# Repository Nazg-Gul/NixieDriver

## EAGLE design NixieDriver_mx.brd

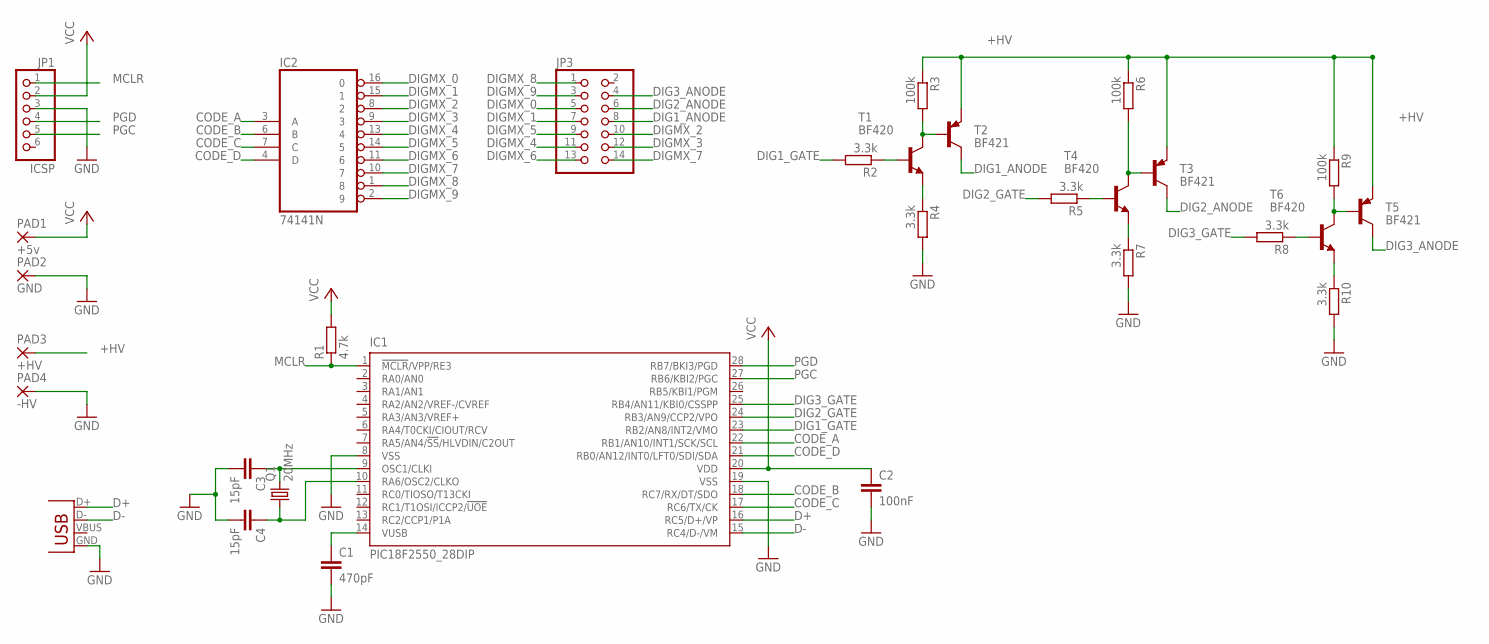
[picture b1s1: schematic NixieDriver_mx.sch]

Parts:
C1: 470pF; C050-024X044
C2: 100nF; C050-024X044
C3, C4: 15pF; C050-024X044
IC1: PIC18F2550_28DIP; DIL28-3
IC2: 74141N; DIL16
JP1: ICSP; 1X06
JP3: PINHD-2X7; 2X07
PAD1: +5v; SMD2,54-5,08
PAD2: GND; SMD2,54-5,08
PAD3: +HV; SMD2,54-5,08
PAD4: -HV; SMD2,54-5,08
Q1: 20MHz; HC49/S
R1: 4.7k; 0207/2V
R2, R5, R8: 3.3k; 0207/2V
R3, R6, R9: 100k; 0207/5V
R4, R7, R10: 3.3k; 0207/7
T1, T4, T6: BF420; TO92-ECB
T2, T3, T5: BF421; TO92-ECB
X1: USB-B-H

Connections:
+HV: PAD3.1, R3.1, R6.1, R9.1, T2.E, T3.E, T5.E
CODE_A: IC1.22 (RB1/AN10/INT1/SCK/SCL), IC2.3 (A)
CODE_B: IC1.18 (RC7/RX/DT/SDO), IC2.6 (B)
CODE_C: IC1.17 (RC6/TX/CK), IC2.7 (C)
CODE_D: IC1.21 (RB0/AN12/INT0/LFT0/SDI/SDA), IC2.4 (D)
D+: IC1.16 (RC5/D+/VP), X1.D+
D-: IC1.15 (RC4/D-/VM), X1.D-
DIG1_ANODE: JP3.8, T2.C
DIG1_GATE: IC1.23 (RB2/AN8/INT2/VMO), R2.2
DIG2_ANODE: JP3.6, T3.C
DIG2_GATE: IC1.24 (RB3/AN9/CCP2/VPO), R5.2
DIG3_ANODE: JP3.4, T5.C
DIG3_GATE: IC1.25 (RB4/AN11/KBI0/CSSPP), R8.2
DIGMX_0: IC2.16 (0), JP3.5
DIGMX_1: IC2.15 (1), JP3.7
DIGMX_2: IC2.8 (2), JP3.10
DIGMX_3: IC2.9 (3), JP3.12
DIGMX_4: IC2.13 (4), JP3.11
DIGMX_5: IC2.14 (5), JP3.9
DIGMX_6: IC2.11 (6), JP3.13
DIGMX_7: IC2.10 (7), JP3.14
DIGMX_8: IC2.1 (8), JP3.1
DIGMX_9: IC2.2 (9), JP3.3
GND: C1.2, C2.2, C3.2, C4.2, IC1.8 (VSS), IC1.19 (VSS), IC2.12 (GND), JP1.3, PAD2.1, PAD4.1, R4.2, R7.2, R10.2, X1.GND
MCLR: IC1.1 (!MCLR!/VPP/RE3), JP1.1, R1.1
unnamed: C1.1, IC1.14 (VUSB)
unnamed: C3.1, IC1.9 (OSC1/CLKI), Q1.2
unnamed: C4.1, IC1.10 (RA6/OSC2/CLKO), Q1.1
unnamed: R3.2, T1.C, T2.B
unnamed: R2.1, T1.B
unnamed: R4.1, T1.E
unnamed: R6.2, T3.B, T4.C
unnamed: R7.1, T4.E
unnamed: R5.1, T4.B
unnamed: R9.2, T5.B, T6.C
unnamed: R10.1, T6.E
unnamed: R8.1, T6.B
PGC: IC1.27 (RB6/KBI2/PGC), JP1.5
PGD: IC1.28 (RB7/BKI3/PGD), JP1.4
VCC: C2.1, IC1.20 (VDD), IC2.5 (VCC), JP1.2, PAD1.1, R1.2

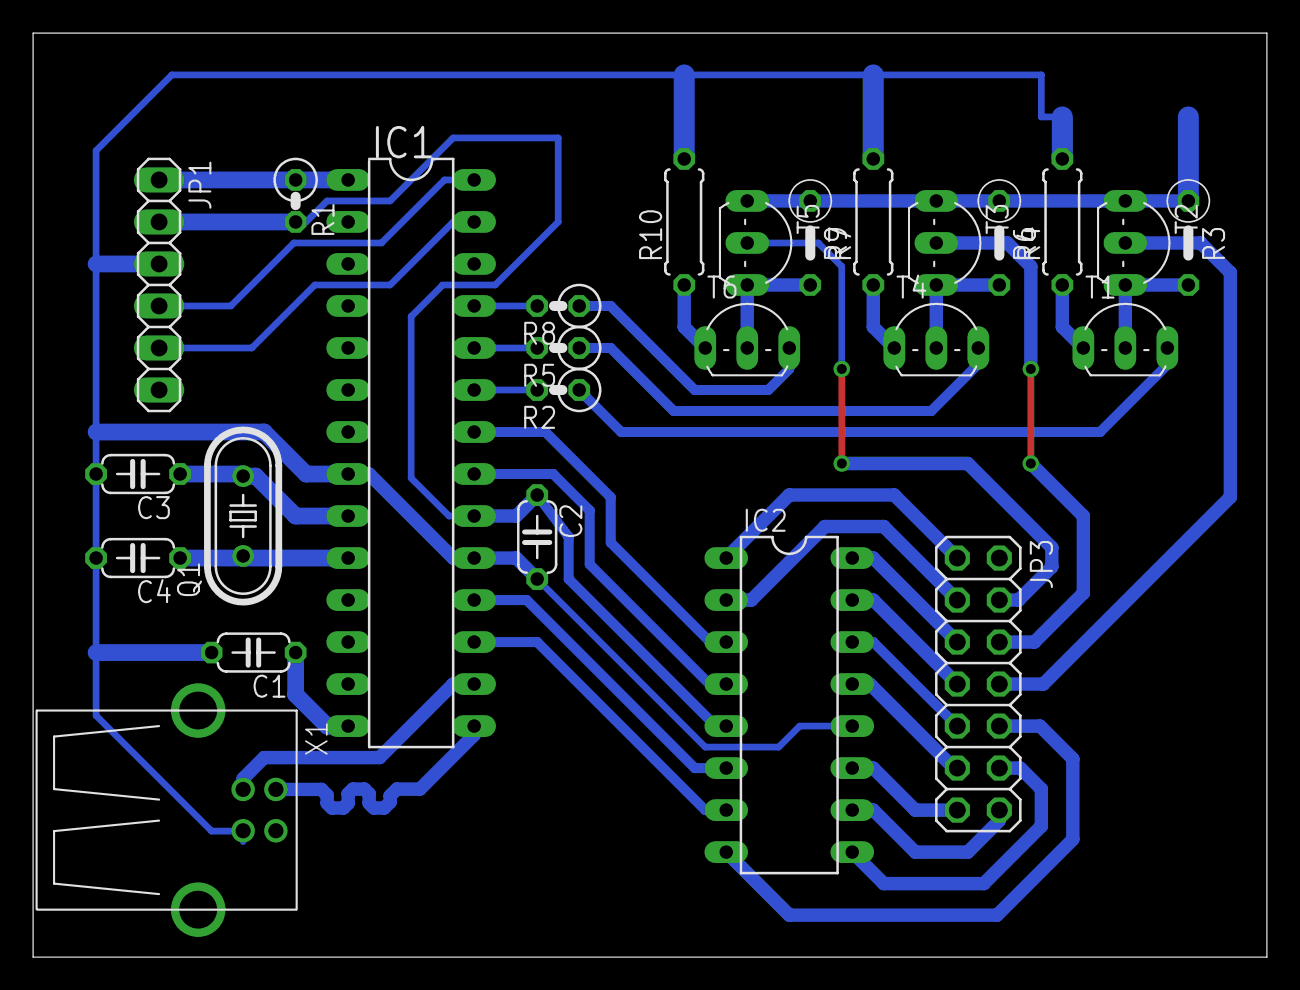
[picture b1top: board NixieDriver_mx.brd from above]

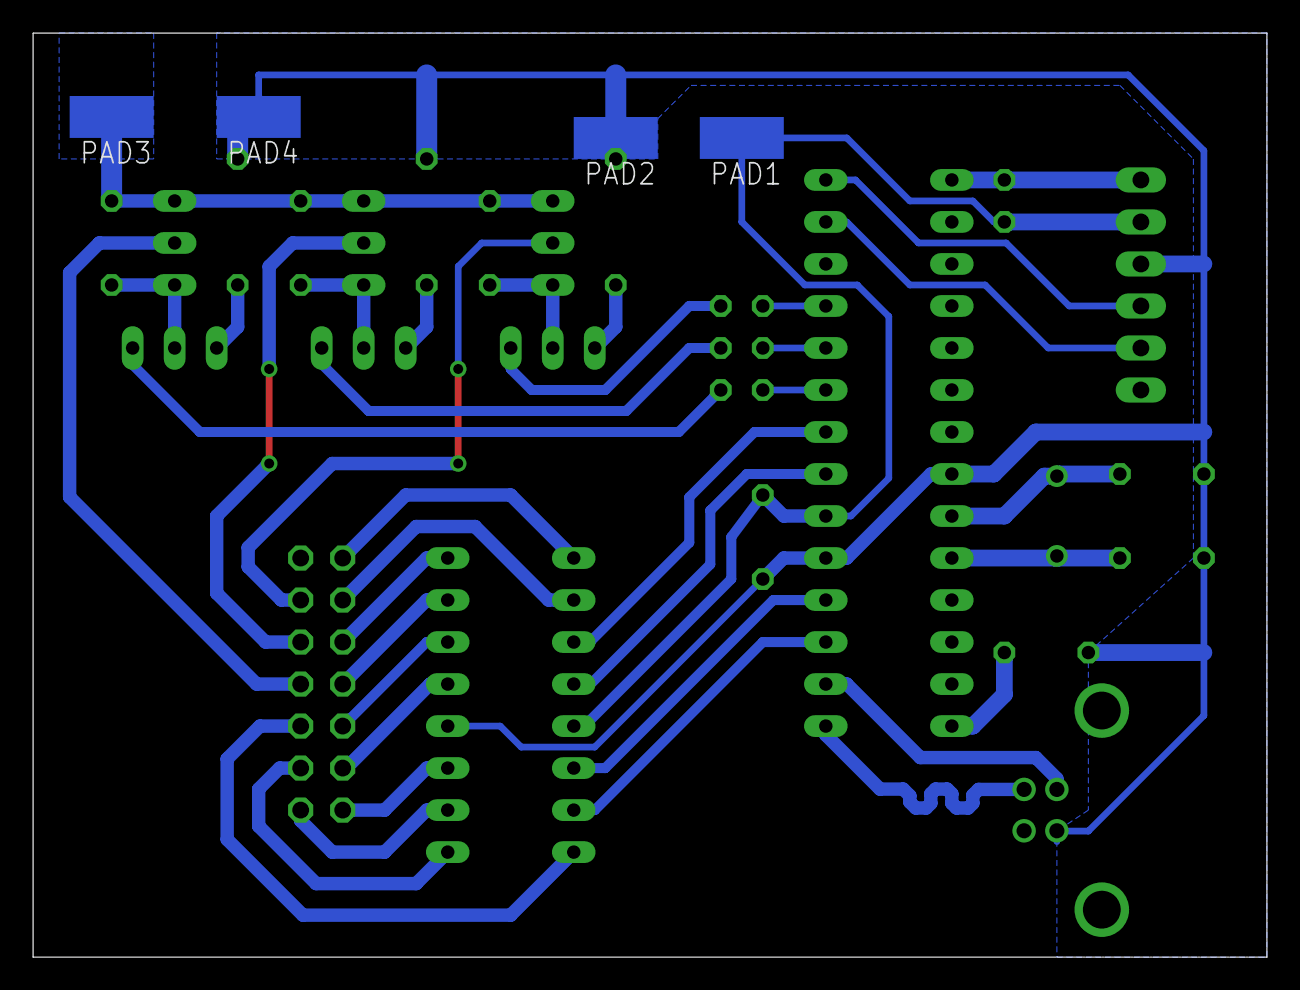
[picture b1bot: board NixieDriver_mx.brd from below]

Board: 2 copper layers, 74.6 x 55.9 mm, 30 parts (4 on the bottom side), 40 nets.

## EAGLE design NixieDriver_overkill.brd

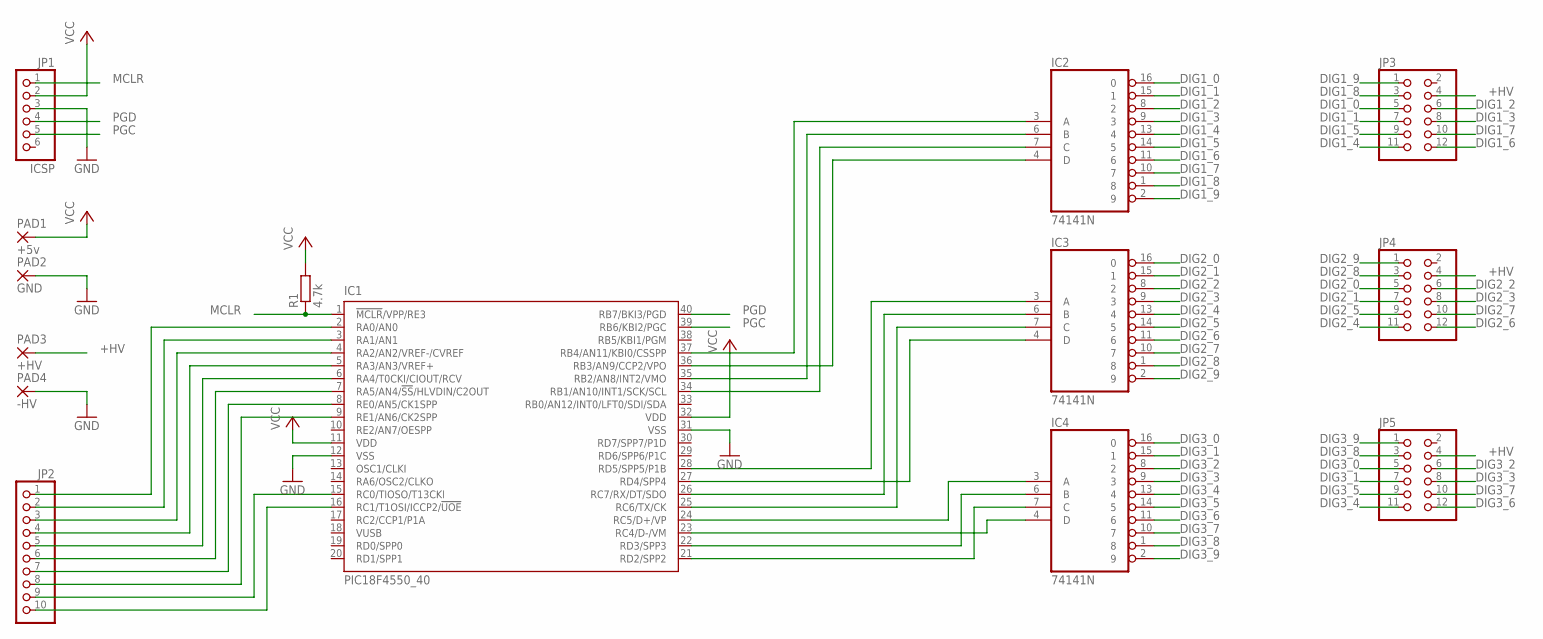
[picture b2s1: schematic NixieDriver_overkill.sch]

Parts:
IC1: PIC18F4550_40; DIL40
IC2, IC3, IC4: 74141N; DIL16
JP1: ICSP; 1X06
JP2: PINHD-1X10; 1X10
JP3, JP4, JP5: PINHD-2X6; 2X06
PAD1: +5v; SMD2,54-5,08
PAD2: GND; SMD2,54-5,08
PAD3: +HV; SMD2,54-5,08
PAD4: -HV; SMD2,54-5,08
R1: 4.7k; R1206

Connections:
+HV: JP3.4, JP4.4, JP5.4, PAD3.1
DIG1_0: IC2.16 (0), JP3.5
DIG1_1: IC2.15 (1), JP3.7
DIG1_2: IC2.8 (2), JP3.6
DIG1_3: IC2.9 (3), JP3.8
DIG1_4: IC2.13 (4), JP3.11
DIG1_5: IC2.14 (5), JP3.9
DIG1_6: IC2.11 (6), JP3.12
DIG1_7: IC2.10 (7), JP3.10
DIG1_8: IC2.1 (8), JP3.3
DIG1_9: IC2.2 (9), JP3.1
DIG2_0: IC3.16 (0), JP4.5
DIG2_1: IC3.15 (1), JP4.7
DIG2_2: IC3.8 (2), JP4.6
DIG2_3: IC3.9 (3), JP4.8
DIG2_4: IC3.13 (4), JP4.11
DIG2_5: IC3.14 (5), JP4.9
DIG2_6: IC3.11 (6), JP4.12
DIG2_7: IC3.10 (7), JP4.10
DIG2_8: IC3.1 (8), JP4.3
DIG2_9: IC3.2 (9), JP4.1
DIG3_0: IC4.16 (0), JP5.5
DIG3_1: IC4.15 (1), JP5.7
DIG3_2: IC4.8 (2), JP5.6
DIG3_3: IC4.9 (3), JP5.8
DIG3_4: IC4.13 (4), JP5.11
DIG3_5: IC4.14 (5), JP5.9
DIG3_6: IC4.11 (6), JP5.12
DIG3_7: IC4.10 (7), JP5.10
DIG3_8: IC4.1 (8), JP5.3
DIG3_9: IC4.2 (9), JP5.1
GND: IC1.12 (VSS), IC1.31 (VSS), IC2.12 (GND), IC3.12 (GND), IC4.12 (GND), JP1.3, PAD2.1, PAD4.1
MCLR: IC1.1 (!MCLR!/VPP/RE3), JP1.1, R1.1
unnamed: IC1.24 (RC5/D+/VP), IC4.3 (A)
unnamed: IC1.23 (RC4/D-/VM), IC4.4 (D)
unnamed: IC1.22 (RD3/SPP3), IC4.6 (B)
unnamed: IC1.21 (RD2/SPP2), IC4.7 (C)
unnamed: IC1.25 (RC6/TX/CK), IC3.7 (C)
unnamed: IC1.26 (RC7/RX/DT/SDO), IC3.6 (B)
unnamed: IC1.27 (RD4/SPP4), IC3.4 (D)
unnamed: IC1.28 (RD5/SPP5/P1B), IC3.3 (A)
unnamed: IC1.34 (RB1/AN10/INT1/SCK/SCL), IC2.7 (C)
unnamed: IC1.35 (RB2/AN8/INT2/VMO), IC2.6 (B)
unnamed: IC1.36 (RB3/AN9/CCP2/VPO), IC2.4 (D)
unnamed: IC1.37 (RB4/AN11/KBI0/CSSPP), IC2.3 (A)
unnamed: IC1.2 (RA0/AN0), JP2.1
unnamed: IC1.3 (RA1/AN1), JP2.2
unnamed: IC1.4 (RA2/AN2/VREF-/CVREF), JP2.3
unnamed: IC1.5 (RA3/AN3/VREF+), JP2.4
unnamed: IC1.6 (RA4/T0CKI/CIOUT/RCV), JP2.5
unnamed: IC1.7 (RA5/AN4/!SS!/HLVDIN/C2OUT), JP2.6
unnamed: IC1.8 (RE0/AN5/CK1SPP), JP2.7
unnamed: IC1.9 (RE1/AN6/CK2SPP), JP2.8
unnamed: IC1.15 (RC0/TIOSO/T13CKI), JP2.9
unnamed: IC1.16 (RC1/T1OSI/ICCP2/!UOE), JP2.10
PGC: IC1.39 (RB6/KBI2/PGC), JP1.5
PGD: IC1.40 (RB7/BKI3/PGD), JP1.4
VCC: IC1.11 (VDD), IC1.32 (VDD), IC2.5 (VCC), IC3.5 (VCC), IC4.5 (VCC), JP1.2, PAD1.1, R1.2

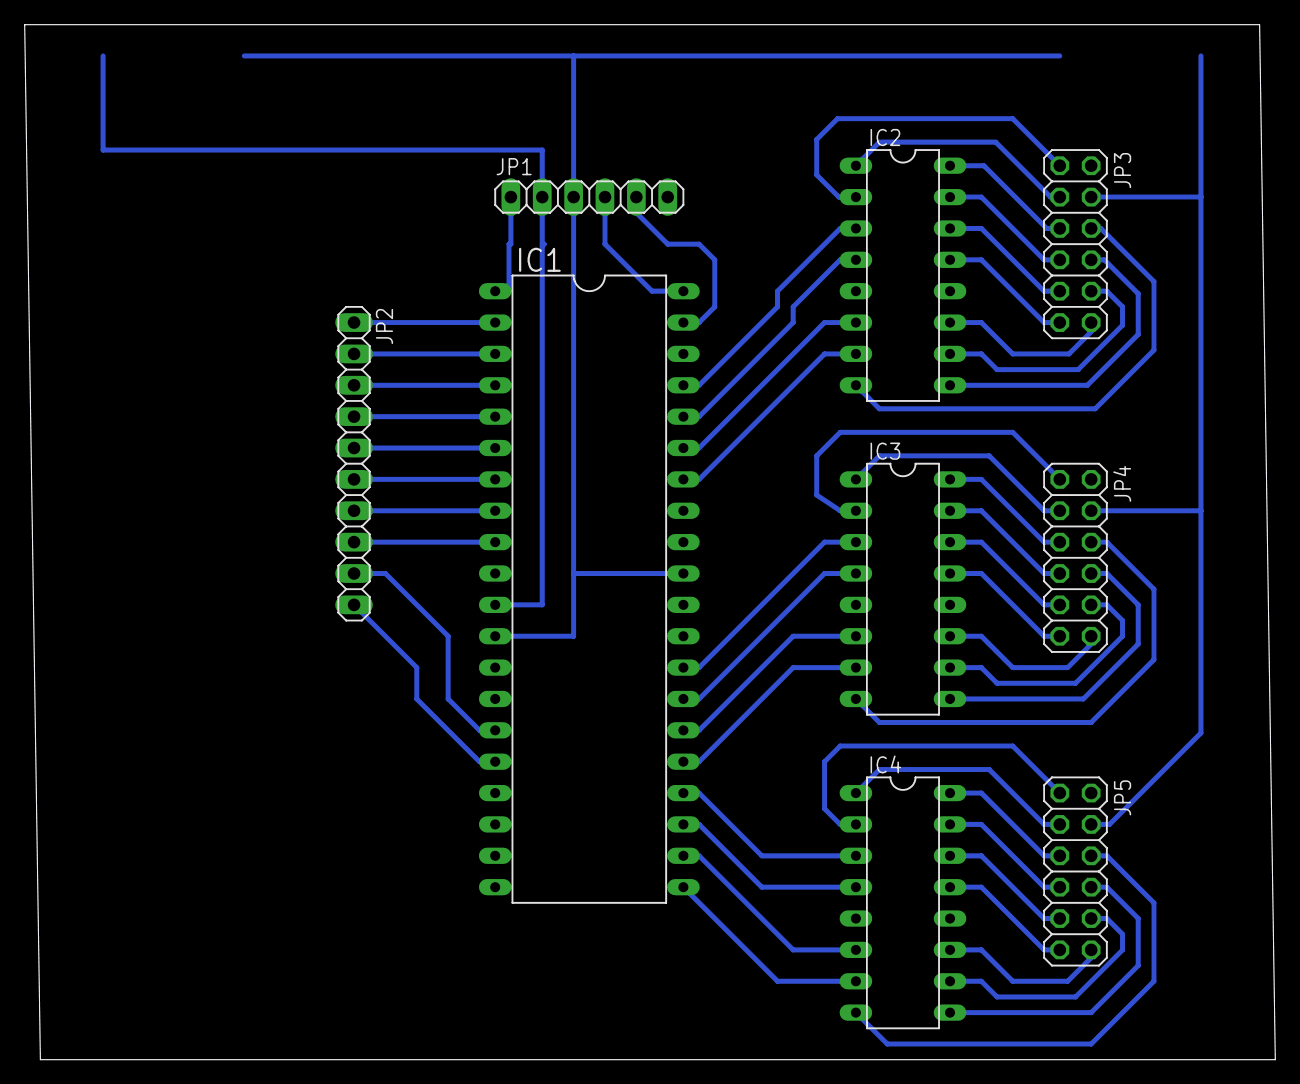
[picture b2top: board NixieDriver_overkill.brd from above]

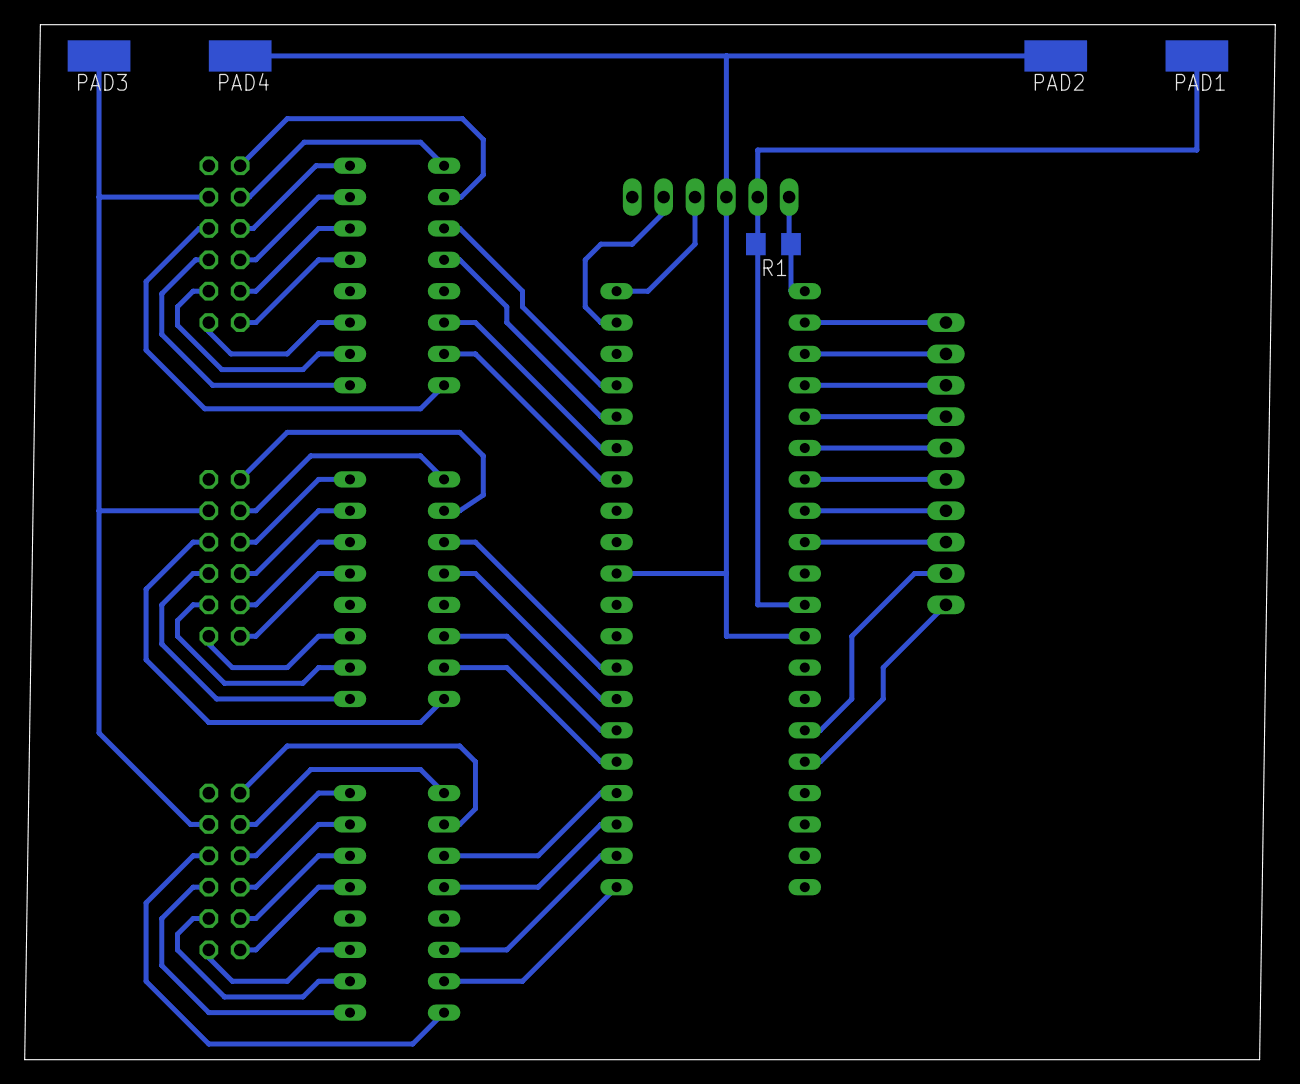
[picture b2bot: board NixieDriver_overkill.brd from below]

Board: 2 copper layers, 101.3 x 83.8 mm, 14 parts (5 on the bottom side), 58 nets.

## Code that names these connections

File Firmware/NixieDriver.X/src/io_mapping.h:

/*
 * ***** BEGIN GPL LICENSE BLOCK *****
 *
 * This program is free software; you can redistribute it and/or
 * modify it under the terms of the GNU General Public License
 * as published by the Free Software Foundation; either version 3
 * of the License, or (at your option) any later version.
 *
 * This program is distributed in the hope that it will be useful,
 * but WITHOUT ANY WARRANTY; without even the implied warranty of
 * MERCHANTABILITY or FITNESS FOR A PARTICULAR PURPOSE.  See the
 * GNU General Public License for more details.
 *
 * You should have received a copy of the GNU General Public License
 * along with this program; if not, write to the Free Software Foundation,
 * Inc., 51 Franklin Street, Fifth Floor, Boston, MA 02110-1301, USA.
 *
 * The Original Code is Copyright (C) 2014 Sergey Sharybin <sergey@blender.org>
 * All rights reserved.
 *
 * Contributor(s): none yet.
 *
 * ***** END GPL LICENSE BLOCK *****
 */

#ifndef __IO_MAPPING_H__
#define __IO_MAPPING_H__

/* We've optimized the routes on PCB, so now we suffer in the firmware by
 * writing to the individual bits
 */

/* Decimal code which is passed to the digital decoder. */
// RIP one of the IO pins...
#define BIN_CODE_0 PORTBbits.RB1
//#define BIN_CODE_0 PORTAbits.RA5
#define BIN_CODE_1 PORTCbits.RC7
#define BIN_CODE_2 PORTCbits.RC6
#define BIN_CODE_3 PORTBbits.RB0

#define BIN_CODE_SEND_CODE(a, b, c, d) { \
    BIN_CODE_0 = a; \
    BIN_CODE_1 = b; \
    BIN_CODE_2 = c; \
    BIN_CODE_3 = d; \
  } (void) 0

#define BIN_CODE_SEND_DIGIT(digit) { \
    BIN_CODE_SEND_CODE(digit & 1, \
                       (digit >> 1) & 1, \
                       (digit >> 2) & 1, \
                       (digit >> 3) & 1);\
  } (void) 0

#define BIN_CODE_SEND_CLOSE() \
  BIN_CODE_SEND_CODE(1, 1, 1, 1)

/* Digit number, for multiplexing, defines which transistor gate is open. */
// RIP one more of the IO pins...
#define DIG_GATE_0 PORTBbits.RB2
//#define DIG_GATE_0 PORTBbits.RB5
#define DIG_GATE_1 PORTBbits.RB3
#define DIG_GATE_2 PORTBbits.RB4

#define DIG_GATE_OPEN(gate) DIG_GATE_ ## gate = 1
#define DIG_GATE_CLOSE(gate) DIG_GATE_ ## gate = 0

#endif  /* __IO_MAPPING_H__ */

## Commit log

2017-01-21 Initial commit of Rev.A
2017-01-21 Dump current status from laptop
